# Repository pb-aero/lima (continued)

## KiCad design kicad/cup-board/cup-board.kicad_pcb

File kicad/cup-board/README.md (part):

# Cup board — one schematic for both earcups

**Status (measured 2026-11-09):** preliminary. One A2 sheet, 102 parts, 112 nets. Netlist matches `doc/design_nets.py`;
ERC 0 errors (6 intended strap warnings). All 102 parts have footprints. The PCB is routed: 0 unconnected pads, 2 parity
warnings (U8 value, J12 BOM flag). **Schematic and layout are not reviewed, and no board is recorded as built.** Published to
the shelf as `reports/peter/LIMA_cup_board.html`. Sheet notes corrected 2026-11-09, text only: netlist identical before and
after. The title block is still empty because Konnect has no tool for it; a text note above it identifies the sheet. Set it in
Eeschema's Page Settings.

**⚠ Before any fab or assembly files:** the PCB's U8 value still says `ADP7118AUJZ-3.3-R7`. Set it to the 2.5 V part in pcbnew
(double-click U8 → Value), not with Update PCB from Schematic. The J9–J11 pinouts are placeholders. See "PCB — 72/38 ring".

**How to read this file:** the status, "What's on it" and "Open items" are current. The dated sections below are the record of
how the design got here, and earlier ones are overtaken by later ones; they carry a note where that matters.

Replaces the separate `cup-a-board` / `cup-b-board` first passes (commits `891d746`, `7ffb480`): per Peter, 2026-10-16, both
cups are now **identical**, so there is one board, fitted twice. Cup R is an assembly variant with J11 not fitted (2026-10-30).

This departs from John's Rev G per-cup map (`docs/two-adau1860-channel-allocation.md` §2),
where cup A carried the boom-mic uplink on ADC2 and cup B carried the DVNC accelerometer there.
Here the accelerometer moves off the analog inputs onto TDM, which frees ADC2 on *both* cups,
and the boom mic is replaced by a third MEMS mic. `[gap]` Rev G's upstream slot map has not
been updated to match — see open items.

## What's on it

| Ref | Part | Connection |
|---|---|---|
| U1 | ADAU1861 | Codec, 3 ADC + 1 DAC (ruled 2026-09-22). REG_EN (pin 28) on 1V8, so the internal regulator makes DVDD (pin 54, net `U1_DVDD`, C47 1 µF + C48 100 nF) |
| J9, J10 | 6-pin 0.5 mm ZIF | MK1 feed-forward and MK2 feedback IM73A135 on Infineon flex: 1 `3V3_MIC` (carries 2.5 V), 2–3 output → AINP0/AINN0 and AINP1/AINN1, 4 NC, 5–6/MP GND. **Pinout is a placeholder** |
| J11 | 6-pin 0.5 mm ZIF | MK3 IM72D128 PDM voice mic on flex, cup L only: 1 `1V8`, 2 `DMIC_DATA` → U1 DMIC01, 3 `DMIC_CLK` ← U1, 4–6/MP GND. **Pinout is a placeholder** |
| C11 | 1 µF | 1V8 decoupling, kept on both cups |
| J7 | 6-pin JST GH | In: 1–2 `A_LINE_P/N` (A2B), 3–4 `XF_SEC_A/B` (this cup's SP-74 secondary, from the audio board), 5–6 `ELEC_HI/LO` (boom electret) |
| J8 | 2-pin JST GH | A2B out to the next cup, unused on the last cup |
| J2 | 2-pin JST GH | Earcup driver, 32 Ω: `SPKR_1/2` from the U4/U5 switch commons |
| J12 | 2 solder pads | Boom electret, to J7.5–6 only |
| U4, U5 | Panasonic AQW612S ×2 | Speaker switch K2, one per leg. **Unpowered (N.C., 7–8 closed): speaker ← SP-74 secondary. Driven (N.O., 5–6 closed): speaker ← HPOUTN/HPOUTP** |
| R7, R8, Q2, R17, R18 | 680 Ω ×2, MMBT3904, 2.2 kΩ, 100 kΩ | K2 drive: U6 IO7 → `K2_CTL` → R17 → Q2 (R18 pull-down) switches the LED returns; LEDs fed from `VIN_CUP` |
| C9/C10, R4/R5, R6 | 1 µF ×2, 10 kΩ ×2, 22 kΩ | ADC2 tap off the SP-74 secondary → AINP2/AINN2 |
| U2 | LSM6DSV16BX | DVNC reference, TDM slave into U1's SPT1 (`TDM_DATA/BCLK/WCLK`); I²C for config |
| U3 | MAXM86161 | In-ear optical HR/SpO₂ module. I²C on the local bus, `PPG_INT` → U6 IO0, LED supply from U9 |
| U6 | AD2428 | Bus-powered A2B sub-node. I²S master to U1's SPT0, I²C master on SDA/SCL. See "A2B sub-node" |
| U7, U8, U9 | TPS62161, ADP7118-2.5, ADP7118-3.3 | From `VIN_CUP`: `1V8`; `3V3_MIC` (**net carries 2.5 V**); `VLED` |
| R1/R2, R3 | 10 kΩ | I²C pull-ups to 1V8; U3 INTB pull-up to 1V8 |
| H1, H2 | M2 | Mounting holes |

Everything else is decoupling and the A2B bus networks in "A2B sub-node". **Removed:** MK1–MK3 (now on flex, 2026-10-27),
J3, J4, J6 (2026-10-23), J5 (2026-10-26), T1 (moved to the audio board, 2026-10-20), H3 (2026-10-27).

### MAXM86161 (U3) — how it's wired and why

`[fetched]` from ADI's MAXM86161 datasheet: 14-pin OLGA 2.9 × 4.3 × 1.4 mm; VLED 3.0–5.5 V;
VLDO (internal 1.8 V LDO output) and VREF (1.21 V) are outputs needing only a 1 µF bypass each;
LED drive full-scale up to 124 mA; I²C address fixed at 0x62; INTB open-drain; GPIO open-drain
or sync input; pins 6/7/8 are internally tied to the LED cathodes and must be left unconnected
(solder only).

*Note 2026-11-09: VLED now comes from U9 on this board, J4 is gone, and `PPG_INT` goes to U6 IO0. The reasoning below stands.*

- **VLED has its own rail and connector (J4), deliberately not the 3V3_MIC rail.** 3.3 V would
  just meet the 3.0 V minimum, but the LED driver pulses up to 124 mA, and putting that on the
  bias supply of all three ANC/voice mics would inject LED-rate noise into the audio path.
- **I²C shares SDA/SCL with U1 and U2, no address clash:** U3 0x62 `[fetched]`, U1 0x64
  (`1100 1 ADDR1 ADDR0` with both straps low — `[repo]` `linux/adau1860-pi5/REGISTER_CONFIG.md`,
  Table 22), U2 0x6A with SA0 low `[assumed — ST's standard LSM6 address; not re-read from the
  LSM6DSV16BX datasheet]`. The existing 10 kΩ pull-ups (R1/R2) serve all three.
- **LDO_EN tied to 1V8** — the module is always on whenever both rails are up. Shutdown is still
  available by register.
- **INTB → `PPG_INT`**, pulled up by R3, brought out as a label for whatever host reads the sensor.
- **GPIO no-connect** (power-on default is tristate).

Because all three mic inputs are now differential, U1's `CM` pin is unused and no-connected
(it was only needed to bias the single-ended boom input in the old cup A).

U1 strap pins as on `audio-board`: ADDR0/ADDR1/SELFBOOT/ROM_BOOT_MODE/REG_EN low, PD high.
U2: CS high (I²C), SA0 low, Qvar electrodes to GND, INT1/INT2 no-connect.
SPT0 (`I2S0_*`) connects to U6, the A2B sub-node (2026-10-23).

## 2026-10-26 — brought in line with the redone audio board, per Peter

Three changes, each checked: netlist == `doc/design_nets.py`, ERC 0 errors (6 strap warnings, unchanged) `[measured]`.

1. **U1 DVDD overvoltage fixed.** Pin 54 (DVDD) had been on 1V8 against a **1.21 V absolute maximum**, with pin 28
   REG_EN grounded `[fetched]` ADAU1861 DS (DVDD 0.85–1.21 V; abs max −0.3 to +1.21 V). Now, per the DS pin table:
   **REG_EN → AVDD (1V8)** so the internal regulator makes DVDD; DVDD on its own net `U1_DVDD` with **C47 1 µF + C48
   100 nF** to ground (*"decouple DVDD to DGND with a 1 uF and 0.1 μF capacitor"*); `#FLG10` PWR_FLAG marks the rail
   as internally driven. Commit `f502399`.
2. **Connectors match the audio board, JST GH 1.25 mm** (J7 became 6-pin on 2026-10-29, see "Boom electret pass-through"). J5 is gone. **J7 (4-pin, SM04B):** 1 `A_LINE_P`,
   2 `A_LINE_N`, 3 `XF_SEC_A`, 4 `XF_SEC_B` — the same order as the audio board's J3 (A2B+, A2B−, speaker pair), so a
   straight 1:1 GH cable joins audio J3 → cup L J7. **J8 (2-pin, SM02B):** A2B out to the next cup. **J2 (2-pin, SM02B):**
   speaker driver. **Cup R needs a split harness into its J7:** pins 1–2 from cup L's J8, pins 3–4 from the audio
   board's J4 — the cost of one board for both cups. (Alternative if that harness is unwelcome: a 6-pin chain that
   carries cup R's speaker pair through cup L — changes the audio board's J3/J4 too. Not done.)
3. **`PPG_INT` → U6 IRQ/IO0 (pin 6).** `[fetched]` AD242x DS Table 15: in slave mode, when not used for mailbox
   interrupts, IRQ/IO0 *"serves as a general-purpose I/O pin with interrupt request input capability"*. MAXM86161 INTB
   is open-drain, pulled up to 1V8 by R3; U6 IOVDD is 1V8, so levels match. Software: configure IO0 as an input with
   falling-edge interrupt; the CM5 already polls `A2B_INTSTAT` (audio-board ruling 11). Not yet checked against the TRM
   register list.

## A2B sub-node — 2026-10-23, per Peter

Peter: *"lets try io7 and add a2b to the cup board"*. The cup is now a **bus-powered AD2428 sub-node** (U6): no power wires
in the cup cable, so everything on the board runs from the A2B bias. Intended connectivity is `doc/design_nets.py` —
the netlist at `b641179` plus these edits — and `python3 -I doc/design_nets.py check <netlist.xml>` diffs it against
the kicad-cli netlist. **Result: OK** (every pre-existing net unchanged, every new net complete) `[measured]`.
ERC 0 errors; 6 warnings, all strap pins tied to rails (the 4 old ones plus U6 ADR1/ADR2). The two single-pin
`I2S0_*` warnings are gone — U6 terminates them.

| Block | Parts | Source |
|---|---|---|
| A side (upstream, J7) | FB1/FB2→ACM (+C12 330 nF), C13 12 pF, L1/L2 180 nH, C14/C15 27 pF, FL1 CMC, R9/R10 120R + C16/C17 33 nF, C18/C19 10 nF series, C20/C21 33 nF, C22 470 nF across | EVAL-AD2428WD1BZ sheet 2, A side, read from a rendered image `[fetched]` |
| Bus power in | L3 (line+ → V_NODE), L4 (line− → GND), D1 ZLLS400 → VIN_CUP, C23/C24 | AD242x DS Fig. 36 (bus-powered sub-node) `[fetched]` |
| B side (downstream, J8) | Q1 AO3401A switched by SWP (R11–R14, C25/C26), L5/L6, same coupling as the audio board's main node | DS Fig. 36 + eval B side |
| U6 | I²S master: DTX0 → `I2S0_SDATAI`, DRX0 ← `I2S0_SDATAO`, BCLK/SYNC → `I2S0_BCLK`/`I2S0_FSYNC`; I²C master on SDA/SCL; IOVDD on 1V8; VOUT1/VOUT2 decoupled | AD242x TRM |
| K2 drive | U6 IO7 → R17 2.2k → Q2 MMBT3904 (R18 100k pull-down) switches U4/U5 LED returns; R7/R8 **680R** from VIN_CUP (220R until the 8 V bus) | audio-board rulings 11, 12 |
| Power | U7 TPS62161 → 1V8, U8 ADP7118-**2.5** → 3V3_MIC (**2.5 V since 2026-10-30**; the 3.3 V part exceeded the IM73A135's 3.0 V abs max; net name kept to spare the routing), U9 ADP7118-3.3 → VLED (separate, as before, to keep PPG pulses off the mic rail) | TPS6216x DS, ADP7118 |

**Removed:** J3 (1V8/3V3_MIC in), J4 (VLED in), J6 (`SW_DRV` in), and the PWR_FLAGs on 3V3_MIC/VLED (the LDOs drive
them now). **Why a BJT for K2:** U6's IO is 1.8 V, too low to turn a 2N7002 on reliably. **Why 680R:** with the AeroNode's 8 V bus (ruling 12) VIN_CUP is 6.4–7.2 V, giving 5.1–7.2 mA per string
(220R would have pushed ~20 mA and wasted ~0.27 W per cup).

**Ground rule `[fetched]` EE-419:** *"the ground of a bus-powered node is not at the same potential as the ground of a
locally-powered node ... only floating signals ... should be connected."* J5 (SP-74 secondary) is transformer-isolated
and reaches U1 only through C9/C10; the speaker reaches it only through K2. The IO7 route also avoided a wired K2 drive
that would have DC-tied the grounds.

### Open — A2B sub-node

- ~~**VIN_CUP margin at low battery.**~~ **Closed 2026-10-23:** `docs/a2b-bus-power-budget.md` → 8 V boost on the audio
  board (ruling 12); cup R VIN 6.44 V worst case.
- ~~**Cup power budget not run**~~ **Run 2026-10-30** — see "Power budget — 2026-10-30": ≈ 41–45 mA per cup normal,
  149 mA for both cups worst case, inside the 300 mA VSSN limit. (Original item:) (U1's HiFi 3z, three mics, LSM6, MAXM86161 LED pulses) against the main node's 300 mA
  VSSN limit for both cups.
- **Sub-node IO7 state on data-link loss with bus power still up** — not in the TRM section read.
- **Cup R's speaker pair** arrives on its J7.3–4 from the audio board's J4; A2B comes from cup L's J8 on J7.1–2.
- ~~**Still unfixed, needs Peter's go-ahead:** U1 DVDD (pin 54) on 1V8 against a 1.21 V abs max (REG_EN low).~~
  **Fixed 2026-10-26** (internal regulator, see above).

## Aircraft audio in — 2026-10-20, per Peter

*Note 2026-11-09: this section's J5 is now J7.3–4, its `SW_DRV`/J6 is now the K2 drive from U6 IO7, and its "T1" is this cup's
SP-74 on the audio board. Its 330 Ω and 5 V drive figures are replaced by 680 Ω from `VIN_CUP`, 5.1–7.2 mA per string.*

Peter ruled: aircraft audio goes into **ADC2 on each cup** (MK3 dropped), the speaker is
**32 Ω**, and the cup must **still be heard unpowered** (fail-passive). Peter proposed the
SP-74 for the bypass path.

```
   audio board                    cable    cup board
 Ring ──┐                 ┌─ J6/J7 ─────── J5 XF_SEC_A ──┬── U4/U5 N.C. ─┐
        SP-74 (pri)   SP-74 (2 sec ∥)                   │               ├─ SPKR_1/2 ── J2 speaker 32 Ω
 Sleeve ┘  T2 / T3        └─ J6/J7 ─────── J5 XF_SEC_B ──┼── U4/U5 N.C. ─┘   U4/U5 N.O. ── HPOUTN / HPOUTP
                                             └── C9/R4, C10/R5, R6 ── AINP2 / AINN2
```

- **Unpowered, or `SW_DRV` dropped:** U4/U5's N.C. switches are closed and T1 drives the speaker. `[derived]` With
  the full primary and the two secondaries in parallel, the turns ratio is 3.143:1, so the
  impedance ratio is 9.88:1 and a 32 Ω speaker looks like **≈ 316 Ω** to the panel. Two cups
  on a mono panel come to ≈ 158 Ω, which is inside the ≥ 150 Ω the panel is rated for.
  `[fetched]` The Garmin GMA 340 is specified at 100 mW per channel into 150 Ω. Against the
  120 Ω series resistor considered first, the transformer is ≈ 3.6 dB louder at the same panel
  voltage and halves the panel loading. Triad's own rating is 80 Ω : **32 Ω with the secondaries
  in series**, or 8 Ω in parallel. We deliberately use the parallel connection with a 32 Ω load,
  so the panel sees 316 Ω and not 80 Ω.
  **Correction, 2026-10-21:** the SP-74 has **no primary centre tap.** DigiKey's "80 CT"
  description is wrong, and Triad's drawing shows pins 1–2 only. My 2026-10-20 note that "the
  centre tap would give 79 Ω" was built on that listing and is withdrawn. The conclusion stands,
  because the full primary was the connection used anyway.

### SP-74 pinout — `[fetched]` Triad datasheet, publish date 2024-05-30 (`docs/datasheets/Triad_SP-74.pdf`)

| Pin | Winding | Dot | Net here |
|---|---|---|---|
| 1 | Primary, 80 Ω, 12.5 Ω DCR | ● | `RX_RING` (audio board; was `AC_AUDIO` here) |
| 2 | Primary | | `AC_GND` (audio board) |
| 3 | Secondary 1 | ● | `XF_SEC_A` |
| 4 | Secondary 1 | | `XF_SEC_B` |
| 5 | Secondary 2 | ● | `XF_SEC_A` |
| 6 | Secondary 2 | | `XF_SEC_B` |

- **Parallel (8 Ω, this design):** 3∥5 and 4∥6, dot to dot. **Series (32 Ω):** link 4–5 and
  take the output across 3–6.
- **Package:** six gold-plated 0.020″ pins, with a tab at pin 1. The body is
  0.410 × 0.310 × 0.465″ max and the leads are 0.750″ min.
  `[derived]` **Two rows of three: 1-3-5 and 2-4-6, with 2 opposite 1, 4 opposite 3 and 6
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
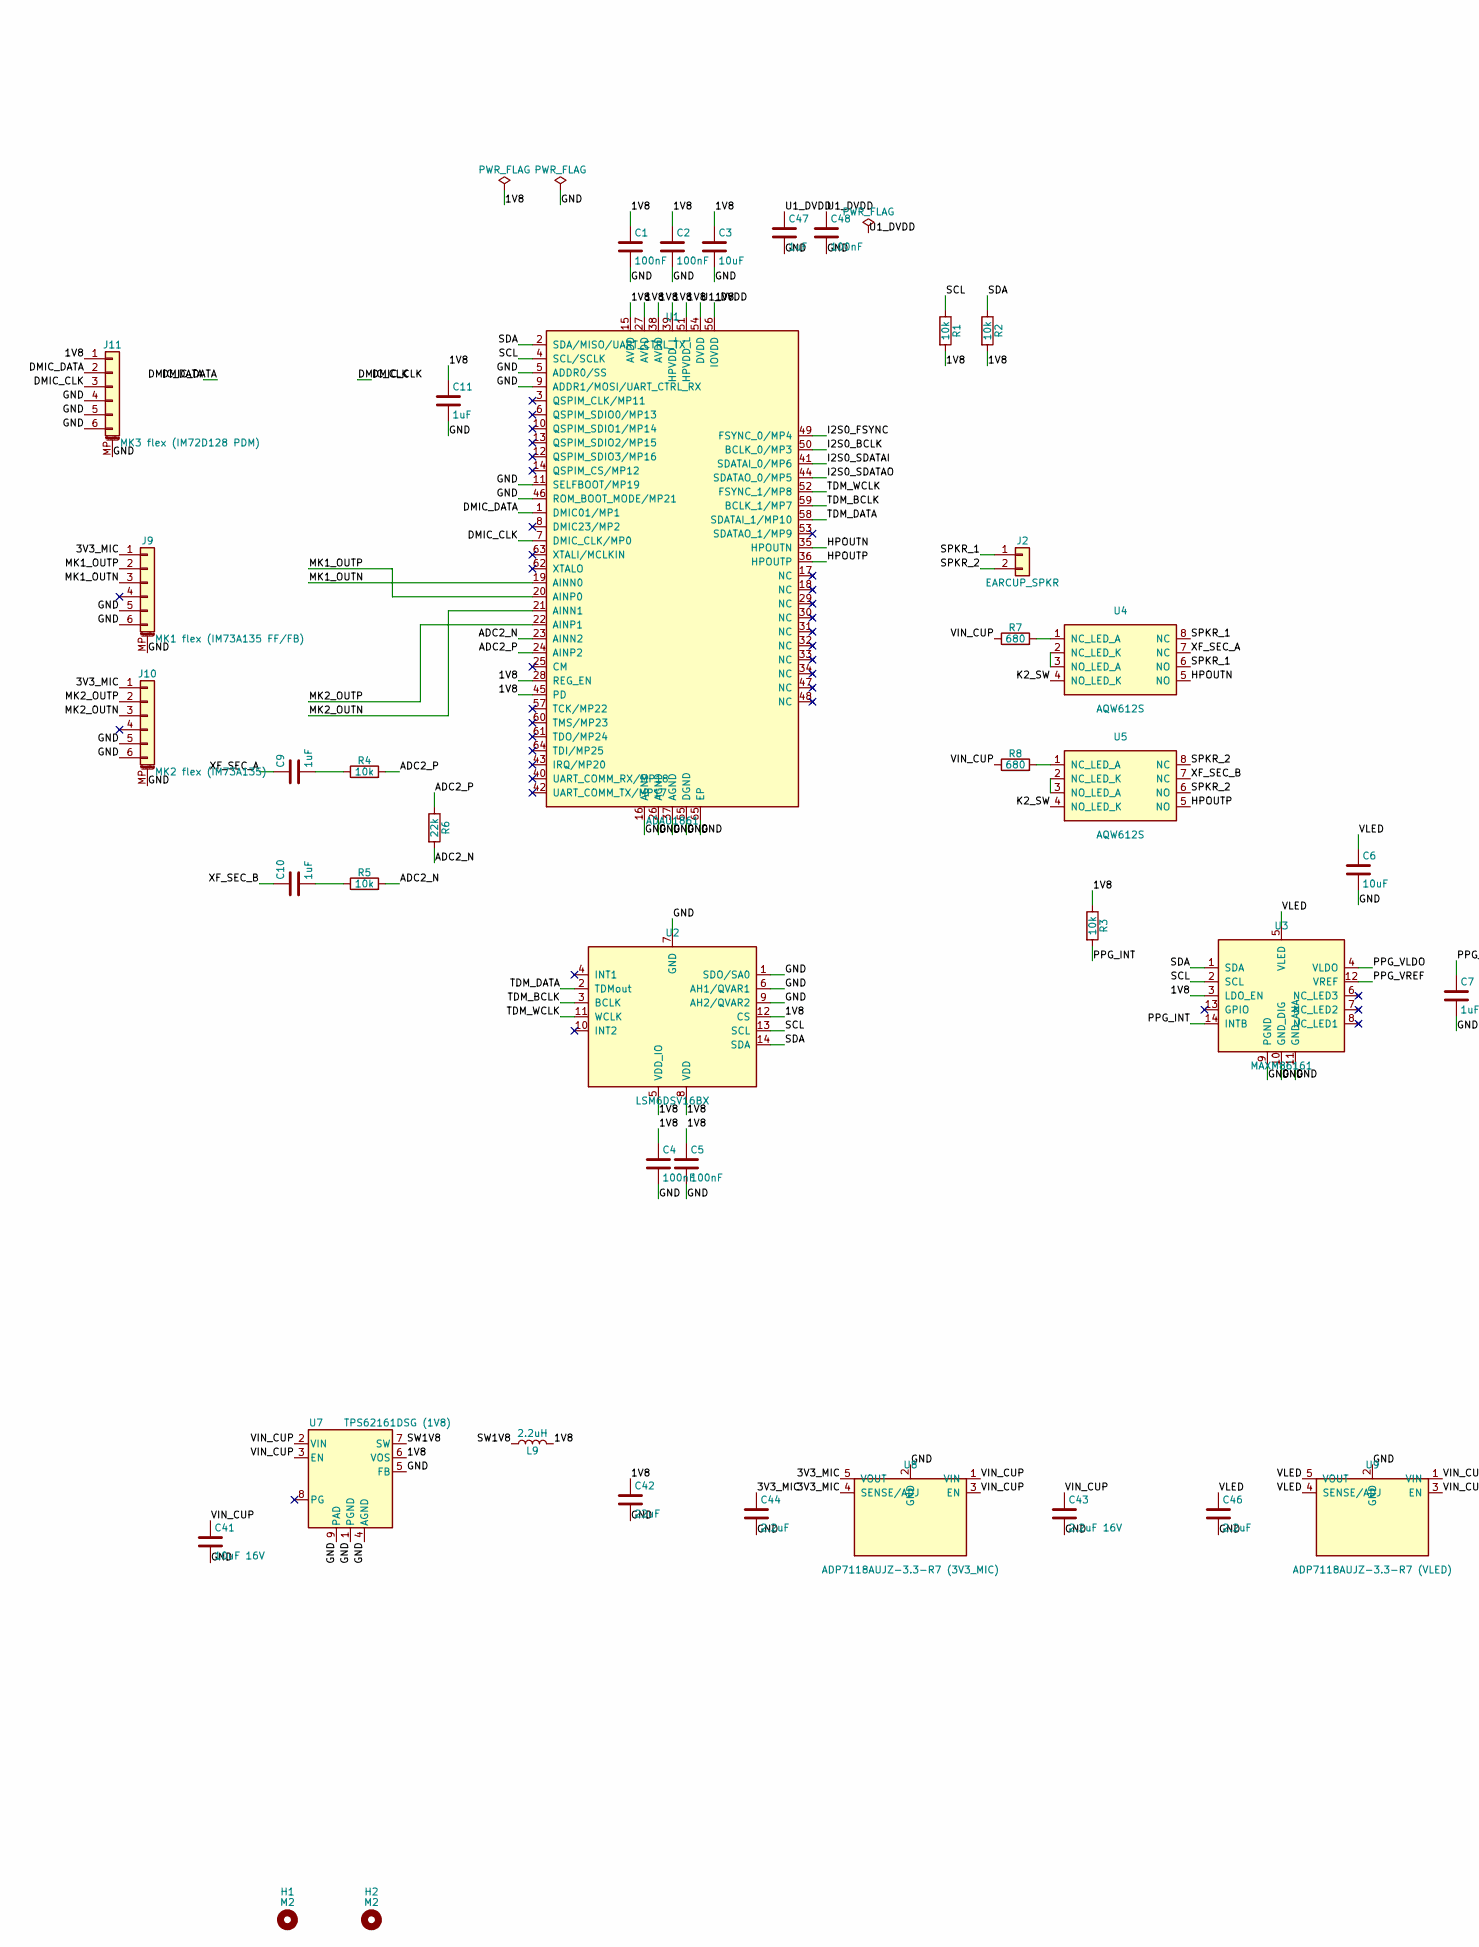
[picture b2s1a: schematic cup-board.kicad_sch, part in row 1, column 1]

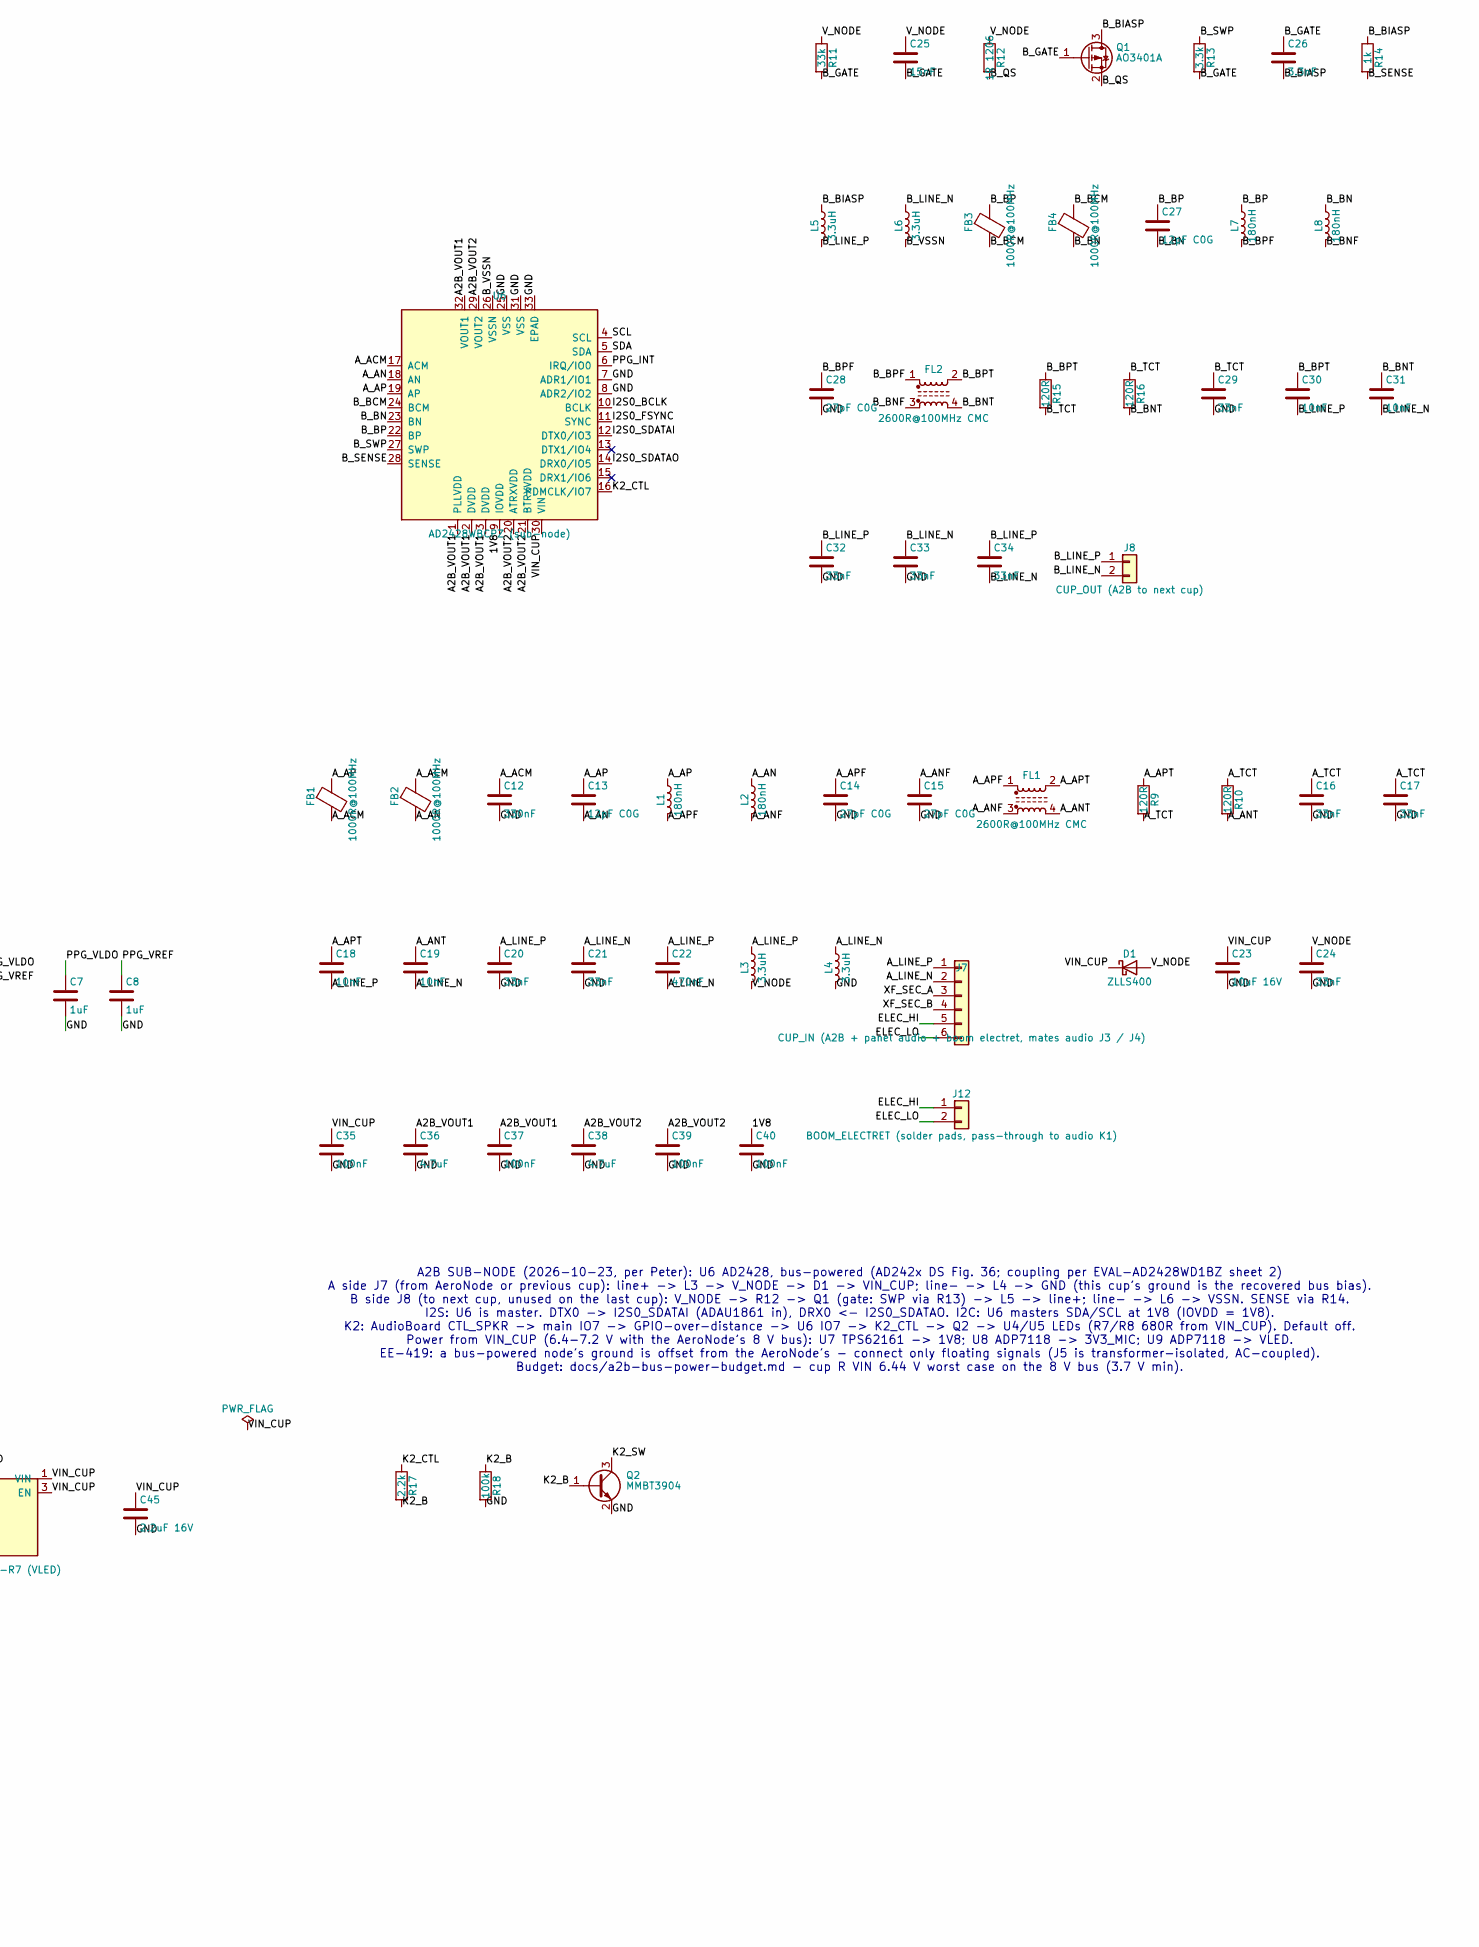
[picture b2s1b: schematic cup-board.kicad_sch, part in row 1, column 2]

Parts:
C1, C2, C4, C5, C35, C37, C39, C40, C48: 100nF; C_0603_1608Metric
C3, C6: 10uF; C_0805_2012Metric
C7, C8, C9, C10, C11, C47: 1uF; C_0603_1608Metric
C12: 330nF; C_0603_1608Metric
C13, C27: 12pF C0G; C_0603_1608Metric
C14, C15, C28: 27pF C0G; C_0603_1608Metric
C16, C17, C20, C21, C24, C29, C32, C33, C34: 33nF; C_0603_1608Metric
C18, C19, C30, C31: 10nF; C_0603_1608Metric
C22: 470nF; C_0603_1608Metric
C23, C41: 10uF 16V; C_0805_2012Metric
C25: 15nF; C_0603_1608Metric
C26: 3.3nF; C_0603_1608Metric
C36, C38: 4.7uF; C_0603_1608Metric
C42: 22uF; C_0805_2012Metric
C43, C45: 2.2uF 16V; C_0603_1608Metric
C44, C46: 2.2uF; C_0603_1608Metric
D1: ZLLS400; D_SOD-323
FB1, FB2, FB3, FB4: 1000R@100MHz; L_0603_1608Metric
FL1, FL2: 2600R@100MHz CMC; L_CommonModeChoke_Coilank_ACM3216
H1, H2: M2; MountingHole_2.2mm_M2
J2: EARCUP_SPKR; JST_GH_SM02B-GHS-TB_1x02-1MP_P1.25mm_Horizontal
J7: CUP_IN (A2B + panel audio + boom electret, mates 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; JST_GH_SM06B-GHS-TB_1x06-1MP_P1.25mm_Horizontal
J8: CUP_OUT (A2B to next cup); JST_GH_SM02B-GHS-TB_1x02-1MP_P1.25mm_Horizontal
J9: MK1 flex (IM73A135 FF/FB); Hirose_FH12-6S-0.5SH_1x06-1MP_P0.50mm_Horizontal; MPN Hirose FH12-6S-0.5SH(55)
J10: MK2 flex (IM73A135); Hirose_FH12-6S-0.5SH_1x06-1MP_P0.50mm_Horizontal; MPN Hirose FH12-6S-0.5SH(55)
J11: MK3 flex (IM72D128 PDM); Hirose_FH12-6S-0.5SH_1x06-1MP_P0.50mm_Horizontal; MPN Hirose FH12-6S-0.5SH(55)
J12: BOOM_ELECTRET (solder pads, pass-through to audio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; SolderWire-0.15sqmm_1x02_P4mm_D0.5mm_OD1.5mm
L1, L2, L7, L8: 180nH; L_0603_1608Metric
L3, L4, L5, L6: 3.3uH; L_1210_3225Metric
L9: 2.2uH; L_1008_2520Metric
Q1: AO3401A; SOT-23
Q2: MMBT3904; SOT-23
R1, R2, R3, R4, R5: 10k; R_0603_1608Metric
R6: 22k; R_0603_1608Metric
R7, R8: 680; R_0603_1608Metric
R9, R10, R15, R16: 120R; R_0603_1608Metric
R11: 33k; R_0603_1608Metric
R12: 1R 1206; R_1206_3216Metric
R13: 3.3k; R_0603_1608Metric
R14: 1k; R_0603_1608Metric
R17: 2.2k; R_0603_1608Metric
R18: 100k; R_0603_1608Metric
U1: ADAU1861; AD_LFCSP-SS-64-1EP_9x9mm_P0.5mm_EP6.3x6.3mm_CS-64-2
U2: LSM6DSV16BX; LGA-14_3x2.5mm_P0.5mm_LayoutBorder3x4y
U3: MAXM86161; Maxim_OLGA-14_2.9x4.3mm_P0.6mm_F142A4_MAXM86161
U4, U5: AQW612S; Panasonic_GU-SOP8_4.4x9.37mm_P2.54mm_AQW61xS
U6: AD2428WBCPZ (sub-node); QFN-32-1EP_5x5mm_P0.5mm_EP3.6x3.6mm_ThermalVias
U7: TPS62161DSG (1V8); WSON-8-1EP_2x2mm_P0.5mm_EP0.9x1.6mm_ThermalVias
U8: ADP7118AUJZ-3.3-R7 (3V3_MIC); TSOT-23-5
U9: ADP7118AUJZ-3.3-R7 (VLED); TSOT-23-5

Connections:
/1V8: C1.1, C2.1, C3.1, C4.1, C5.1, C11.1, C40.1, C42.1, J11.1, L9.2, R1.2, R2.2, R3.1, U1.15 (AVDD), U1.27 (AVDD), U1.28 (REG_EN), U1.38 (AVDD), U1.39 (HPVDD_L), U1.45 (PD), U1.51 (HPVDD_L), U1.56 (IOVDD), U2.5 (VDD_IO), U2.8 (VDD), U2.12 (CS), U3.3 (LDO_EN), U6.9 (IOVDD), U7.6 (VOS)
/3V3_MIC: C44.1, J9.1, J10.1, U8.4 (SENSE/ADJ), U8.5 (VOUT)
/A2B_VOUT1: C36.1, C37.1, U6.1 (PLLVDD), U6.2 (DVDD), U6.3 (DVDD), U6.32 (VOUT1)
/A2B_VOUT2: C38.1, C39.1, U6.20 (ATRXVDD), U6.21 (BTRXVDD), U6.29 (VOUT2)
/ADC2_N: R5.2, R6.2, U1.23 (AINN2)
/ADC2_P: R4.2, R6.1, U1.24 (AINP2)
/A_ACM: C12.1, FB1.2, FB2.1, U6.17 (ACM)
/A_AN: C13.2, FB2.2, L2.1, U6.18 (AN)
/A_ANF: C15.1, FL1.3, L2.2
/A_ANT: C19.1, FL1.4, R10.2
/A_AP: C13.1, FB1.1, L1.1, U6.19 (AP)
/A_APF: C14.1, FL1.1, L1.2
/A_APT: C18.1, FL1.2, R9.1
/A_LINE_N: C19.2, C21.1, C22.2, J7.2, L4.1
/A_LINE_P: C18.2, C20.1, C22.1, J7.1, L3.1
/A_TCT: C16.1, C17.1, R9.2, R10.1
/B_BCM: FB3.2, FB4.1, U6.24 (BCM)
/B_BIASP: C26.2, L5.1, Q1.3 (D), R14.1
/B_BN: C27.2, FB4.2, L8.1, U6.23 (BN)
/B_BNF: FL2.3, L8.2
/B_BNT: C31.1, FL2.4, R16.2
/B_BP: C27.1, FB3.1, L7.1, U6.22 (BP)
/B_BPF: C28.1, FL2.1, L7.2
/B_BPT: C30.1, FL2.2, R15.1
/B_GATE: C25.2, C26.1, Q1.1 (G), R11.2, R13.2
/B_LINE_N: C31.2, C33.1, C34.2, J8.2, L6.1
/B_LINE_P: C30.2, C32.1, C34.1, J8.1, L5.2
/B_QS: Q1.2 (S), R12.2
/B_SENSE: R14.2, U6.28 (SENSE)
/B_SWP: R13.1, U6.27 (SWP)
/B_TCT: C29.1, R15.2, R16.1
/B_VSSN: L6.2, U6.26 (VSSN)
/DMIC_CLK: J11.3, U1.7 (DMIC_CLK/MP0)
/DMIC_DATA: J11.2, U1.1 (DMIC01/MP1)
/ELEC_HI: J7.5, J12.1
/ELEC_LO: J7.6, J12.2
/GND: C1.2, C2.2, C3.2, C4.2, C5.2, C6.2, C7.2, C8.2, C11.2, C12.2, C14.2, C15.2, C16.2, C17.2, C20.2, C21.2, C23.2, C24.2, C28.2, C29.2, C32.2, C33.2, C35.2, C36.2, C37.2, C38.2, C39.2, C40.2, C41.2, C42.2, C43.2, C44.2, C45.2, C46.2, C47.2, C48.2, J9.5, J9.6, J9.MP (MountPin), J10.5, J10.6, J10.MP (MountPin), J11.4, J11.5, J11.6, J11.MP (MountPin), L4.2, Q2.2 (E), R18.2, U1.5 (ADDR0/SS), U1.9 (ADDR1/MOSI/UART_CTRL_RX), U1.11 (SELFBOOT/MP19), U1.16 (AGND), U1.26 (AGND), U1.37 (AGND), U1.46 (ROM_BOOT_MODE/MP21), U1.55 (DGND), U1.65 (EP), U2.1 (SDO/SA0), U2.6 (AH1/QVAR1), U2.7 (GND), U2.9 (AH2/QVAR2), U3.9 (PGND), U3.10 (GND_DIG), U3.11 (GND_ANA), U6.7 (ADR1/IO1), U6.8 (ADR2/IO2), U6.25 (VSS), U6.31 (VSS), U6.33 (EPAD), U7.1 (PGND), U7.4 (AGND), U7.5 (FB), U7.9 (PAD), U8.2 (GND), U9.2 (GND)
/HPOUTN: U1.35 (HPOUTN), U4.5 (NO)
/HPOUTP: U1.36 (HPOUTP), U5.5 (NO)
/I2S0_BCLK: U1.50 (BCLK_0/MP3), U6.10 (BCLK)
/I2S0_FSYNC: U1.49 (FSYNC_0/MP4), U6.11 (SYNC)
/I2S0_SDATAI: U1.41 (SDATAI_0/MP6), U6.12 (DTX0/IO3)
/I2S0_SDATAO: U1.44 (SDATAO_0/MP5), U6.14 (DRX0/IO5)
/K2_B: Q2.1 (B), R17.2, R18.1
/K2_CTL: R17.1, U6.16 (PDMCLK/IO7)
/K2_SW: Q2.3 (C), U4.4 (NO_LED_K), U5.4 (NO_LED_K)
/MK1_OUTN: J9.3, U1.19 (AINN0)
/MK1_OUTP: J9.2, U1.20 (AINP0)
/MK2_OUTN: J10.3, U1.21 (AINN1)
/MK2_OUTP: J10.2, U1.22 (AINP1)
/PPG_INT: R3.2, U3.14 (INTB), U6.6 (IRQ/IO0)
/PPG_VLDO: C7.1, U3.4 (VLDO)
/PPG_VREF: C8.1, U3.12 (VREF)
/SCL: R1.1, U1.4 (SCL/SCLK), U2.13 (SCL), U3.2 (SCL), U6.4 (SCL)
/SDA: R2.1, U1.2 (SDA/MISO/UART_CTRL_TX), U2.14 (SDA), U3.1 (SDA), U6.5 (SDA)
/SPKR_1: J2.1, U4.6 (NO), U4.8 (NC)
/SPKR_2: J2.2, U5.6 (NO), U5.8 (NC)
/SW1V8: L9.1, U7.7 (SW)
/TDM_BCLK: U1.59 (BCLK_1/MP7), U2.3 (BCLK)
/TDM_DATA: U1.58 (SDATAI_1/MP10), U2.2 (TDMout)
/TDM_WCLK: U1.52 (FSYNC_1/MP8), U2.11 (WCLK)
/U1_DVDD: C47.1, C48.1, U1.54 (DVDD)
/VIN_CUP: C23.1, C35.1, C41.1, C43.1, C45.1, D1.1 (K), R7.1, R8.1, U6.30 (VIN), U7.2 (VIN), U7.3 (EN), U8.1 (VIN), U8.3 (EN), U9.1 (VIN), U9.3 (EN)
/VLED: C6.1, C46.1, U3.5 (VLED), U9.4 (SENSE/ADJ), U9.5 (VOUT)
/V_NODE: C24.1, C25.1, D1.2 (A), L3.2, R11.1, R12.1
/XF_SEC_A: C9.1, J7.3, U4.7 (NC)
/XF_SEC_B: C10.1, J7.4, U5.7 (NC)
unnamed: C9.2, R4.1
unnamed: C10.2, R5.1
unnamed: R7.2, U4.1 (NC_LED_A)
unnamed: U4.2 (NC_LED_K), U4.3 (NO_LED_A)
unnamed: R8.2, U5.1 (NC_LED_A)
unnamed: U5.2 (NC_LED_K), U5.3 (NO_LED_A)

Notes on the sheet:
A2B SUB-NODE (2026-10-23, per Peter): U6 AD2428, bus-powered (AD242x DS Fig. 36; coupling per EVAL-AD2428WD1BZ sheet 2) A side J7 (from AeroNode or previous cup): line+ -> L3 -> V_NODE -> D1 -> VIN_CUP; line- -> L4 -> GND (this cup's ground is the recovered bus bias). B side J8 (to next cup, unused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

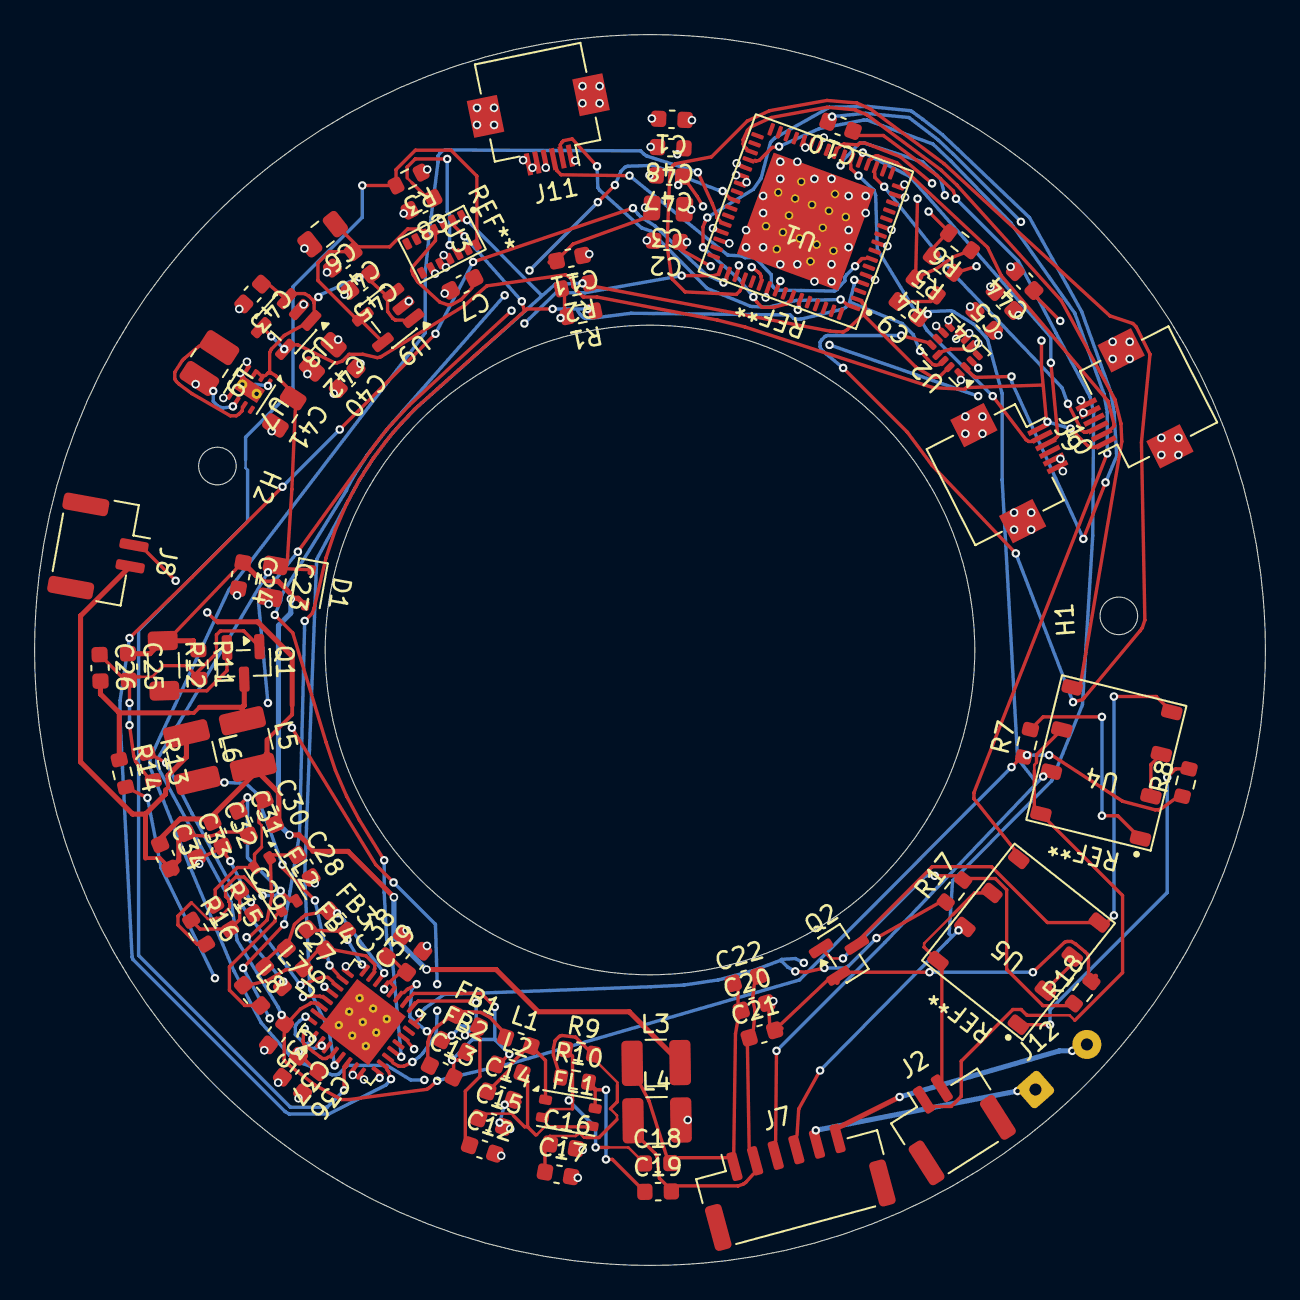
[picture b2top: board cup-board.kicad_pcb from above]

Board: 4 copper layers, 72.0 x 72.0 mm, 102 parts (0 on the bottom side), 73 nets.

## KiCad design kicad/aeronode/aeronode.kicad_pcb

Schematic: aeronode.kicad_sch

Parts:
C1, C9, C10, C11, C12, C15, C18: 10uF; C_0603_1608Metric
C2: 47uF; C_0805_2012Metric
C3, C13, C14, C16, C17, C19, C20, C21, C22: 100nF; C_0402_1005Metric
C4: 1uF; C_0603_1608Metric
C5: 0.22uF; C_0402_1005Metric
C6, C7: 47nF; C_0402_1005Metric
C8: 4.7uF; C_0603_1608Metric
D1: CHG; LED_0603_1608Metric
D2: RED; LED_0603_1608Metric
D3: GREEN; LED_0603_1608Metric
D4: BLUE; LED_0603_1608Metric
J1: IMU_BOARD; PinHeader_2x10_P2.54mm_Vertical
J2: USB-C PD / recovery; USB_C_Receptacle_HCTL_HC-TYPE-C-16P-01A
J3: 2S LiFePO4 6Ah + BMS; PinHeader_1x03_P2.54mm_Vertical
L1: 4.7uH; L_Bourns-SRN6028
L2: 1.0uH; L_Bourns-SRN4018
Q1: NMOS pass - TBD; SOT-23
R1, R9, R14: 100k; R_0402_1005Metric
R2: 6.04k; R_0402_1005Metric
R3, R5, R7, R8: 5.1k; R_0402_1005Metric
R4, R6, R15: 1k; R_0402_1005Metric
R10: 24.9k; R_0402_1005Metric
R11, R12, R13, R17, R19, R21, R31: 10k; R_0402_1005Metric
R16: 34k; R_0402_1005Metric
R18: 22.1k; R_0402_1005Metric
R20: 30.1k; R_0402_1005Metric
R22: 15m; R_1206_3216Metric
R23: 5.24k; R_0402_1005Metric
R24: 30.31k; R_0402_1005Metric
R25, R26: 4.7k; R_0402_1005Metric
R27: 100R; R_0402_1005Metric
R28: 160R; R_0402_1005Metric
R29: 150R; R_0402_1005Metric
R30: 68R; R_0402_1005Metric
SW1: ON/OFF; SW_Push_1P1T_NO_CK_KMR2
U1: ConnectCore93_LGA; Digi_ConnectCore93_LGA
U2: CYPD3177-24LQ; QFN-24-1EP_4x4mm_P0.5mm_EP2.75x2.75mm
U3: BQ25798; Texas_RQM0029A_VQFN-29_4x4mm_P0.4mm
U4: LMR33630ADDA; Texas_HSOP-8-1EP_3.9x4.9mm_P1.27mm_ThermalVias
U5: LTC4364CMS; MSOP-16_3x4.039mm_P0.5mm
U6: BME690; Bosch_LGA-8_3x3mm_P0.8mm_ClockwisePinNumbering; MPN BME690
U7: DAN-F10N; ublox_DAN-F10N; MPN DAN-F10N-00B
U9: MMC5983MA; LGA-16_3x3mm_P0.5mm; MPN MMC5983MA
U10: BMP390; Bosch_BMP390_LGA-10_2x2mm; MPN BMP390

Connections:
/+1V8: U1.AH1 (1V8), U1.AH2 (1V8), U1.AH3 (1V8), U1.E5 (1V8)
/+3V3: C13.1, C14.1, C15.1, C16.1, C19.1, C20.1, C21.1, C22.1, J1.1, R11.1, R12.1, R13.1, R14.1, R15.1, R25.1, R26.1, R28.1, R29.1, R30.1, R31.1, U1.AK1 (3V3), U1.AL2 (3V3), U1.AL3 (3V3), U1.AM3 (3V3), U1.AM4 (3V3), U6.2 (CSB), U6.6 (VDDIO), U6.8 (VDD), U7.52 (VCC), U7.53 (VCC), U7.55 (V_BCKP), U9.2 (VDD), U9.4 (SPI_CS), U9.13 (VDDIO), U10.1 (VDDIO), U10.6 (CSB), U10.10 (VDD)
/+5V: R20.1, R22.2, U1.AJ2 (VSYS2), U1.AJ3 (VSYS2), U1.AJ4 (VSYS2), U1.AK2 (VSYS2), U1.AK3 (VSYS2), U1.AK4 (VSYS2), U1.AL6 (VSYS), U1.AL7 (VSYS), U1.AL8 (VSYS), U5.1 (OUT)
/+5V_RAW: C2.1, L1.2, Q1.3 (D), R9.1, R16.1, R18.1, U5.8 (VCC), U5.9 (~SHDN)
/BARO_SA0: R31.2, U10.5 (SDO)
/BAT_TS: J3.2, R23.2, R24.1, U3.16 (TS)
/BMI_ACC_CS: J1.16, U1.P1 (UART7_TX)
/BMI_ACC_INT: J1.19, U1.AA1 (GPIO2_IO06)
/BMI_GYR_CS: J1.17, U1.C24 (GPIO2_IO24)
/BMI_GYR_INT: J1.20, U1.Y1 (GPIO1_IO10)
/BMI_MOSI: J1.13, U1.M29 (UART7_CTS)
/BMI_SCLK: J1.11, U1.N29 (UART7_RTS)
/BMI_SDO: J1.14, J1.15, U1.R1 (UART7_RX)
/BOOT_5V: C3.1, U4.7 (BOOT)
/CC1: J2.A5 (CC1), U2.15 (CC1)
/CC2: J2.B5 (CC2), U2.14 (CC2)
/CHG_BTST1: C6.1, U3.4 (BTST1)
/CHG_BTST2: C7.1, U3.19 (BTST2)
/CHG_CE_N: R1.2, U1.AN4 (GPIO2_IO18), U3.13 (~CE)
/CHG_INT_N: R13.2, U1.E3 (GPIO2_IO19), U3.21 (~INT)
/CHG_LED_A: D1.2 (A), R15.2
/CHG_PMID: C10.1, U3.29 (PMID)
/CHG_PROG: R2.1, U3.20 (PROG)
/CHG_SCL: R11.2, U1.V1 (I2C2_SCL), U3.14 (SCL)
/CHG_SDA: R12.2, U1.W1 (I2C2_SDA), U3.15 (SDA)
/CHG_STAT_N: D1.1 (K), U3.1 (STAT)
/CHG_SW1: C6.2, L2.1, U3.28 (SW1)
/CHG_SW2: C7.2, L2.2, U3.26 (SW2)
/FB_5V: R9.2, R10.1, U4.5 (FB)
/GND: C1.2, C2.2, C4.2, C5.2, C8.2, C9.2, C10.2, C11.2, C12.2, C13.2, C14.2, C15.2, C16.2, C17.2, C18.2, C19.2, C20.2, C21.2, C22.2, J1.2, J1.4, J1.8, J1.12, J1.18, J2.A1 (GND), J2.A12 (GND), J2.B1 (GND), J2.B12 (GND), J2.SH (SHIELD), J3.3, R2.2, R4.2, R6.2, R8.2, R10.2, R17.2, R19.2, R21.2, R24.2, SW1.2, U1.A4 (GND), U1.A5 (GND), U1.A25 (GND), U1.AF2 (GND), U1.AF3 (GND), U1.AF4 (GND), U1.AF5 (GND), U1.AF6 (GND), U1.AF7 (GND), U1.AF8 (GND), U1.AF9 (GND), U1.AF10 (GND), U1.AF11 (GND), U1.AF12 (GND), U1.AF13 (GND), U1.AF14 (GND), U1.AF15 (GND), U1.AF16 (GND), U1.AF17 (GND), U1.AF18 (GND), U1.AF19 (GND), U1.AF20 (GND), U1.AF21 (GND), U1.AF22 (GND), U1.AF23 (GND), U1.AF24 (GND), U1.AF25 (GND), U1.AF26 (GND), U1.AF27 (GND), U1.AF28 (GND), U1.AG2 (GND), U1.AG3 (GND), U1.AG4 (GND), U1.AG5 (GND), U1.AG6 (GND), U1.AG7 (GND), U1.AG16 (GND), U1.AG23 (GND), U1.AH4 (GND), U1.AH5 (GND), U1.AH8 (GND), U1.AH14 (GND), U1.AH17 (GND), U1.AH19 (GND), U1.AH21 (GND), U1.AJ1 (GND), U1.AJ5 (GND), U1.AJ6 (GND), U1.AJ7 (GND), U1.AJ9 (GND), U1.AJ14 (GND), U1.AJ17 (GND), U1.AJ20 (GND), U1.AJ26 (GND), U1.AK5 (GND), U1.AK6 (GND), U1.AK7 (GND), U1.AK8 (GND), U1.AK9 (GND), U1.AK10 (GND), U1.AK11 (GND), U1.AK12 (GND), U1.AK13 (GND), U1.AK14 (GND), U1.AK17 (GND), U1.AK20 (GND), U1.AK23 (GND), U1.AL4 (GND), U1.AL5 (GND), U1.AL9 (GND), U1.AL10 (GND), U1.AL11 (GND), U1.AL14 (GND), U1.AL17 (GND), U1.AM5 (GND), U1.AM6 (GND), U1.AM12 (GND), U1.AM15 (GND), U1.AM18 (GND), U1.AM20 (GND), U1.AN8 (GND), U1.AN11 (GND), U1.AN14 (GND), U1.AN17 (GND), U1.AN20 (GND), U1.B3 (GND), U1.B4 (GND), U1.B5 (GND), U1.B8 (GND), U1.B11 (GND), U1.B14 (GND), U1.B15 (GND), U1.B18 (GND), U1.B25 (GND), U1.B26 (GND), U1.B27 (GND), U1.C2 (GND), U1.C4 (GND), U1.C5 (GND), U1.C12 (GND), U1.C13 (GND), U1.C14 (GND), U1.C15 (GND), U1.C16 (GND), U1.C25 (GND), U1.C26 (GND), U1.C28 (GND), U1.D2 (GND), U1.D3 (GND), U1.D4 (GND), U1.D16 (GND), U1.D24 (GND), U1.D26 (GND), U1.D27 (GND), U1.D28 (GND), U1.D29 (GND), U1.E1 (GND), U1.E2 (GND), U1.E6 (GND), U1.E8 (GND), U1.E15 (GND), U1.F15 (GND), U1.F16 (GND), U1.F21 (GND), U1.F22 (GND), U1.G5 (GND), U1.G8 (GND), U1.G11 (GND), U1.G16 (GND), U1.G19 (GND), U1.G22 (GND), U1.G25 (GND), U1.G26 (GND), U1.G27 (GND), U1.G28 (GND), U1.H2 (GND), U1.H3 (GND), U1.H4 (GND), U1.H5 (GND), U1.H6 (GND), U1.H7 (GND), U1.H8 (GND), U1.H9 (GND), U1.H10 (GND), U1.H11 (GND), U1.H12 (GND), U1.H13 (GND), U1.H14 (GND), U1.H15 (GND), U1.H16 (GND), U1.H17 (GND), U1.H18 (GND), U1.H19 (GND), U1.H20 (GND), U1.H21 (GND), U1.H22 (GND), U1.H23 (GND), U1.H24 (GND), U1.H25 (GND), U1.H26 (GND), U1.H27 (GND), U1.H28 (GND), U1.H29 (GND), U1.M1 (GND), U1.T1 (GND), U1.Y29 (GND), U2.6 (ISNK_FINE), U2.19 (GND), U2.22 (GND), U2.25 (GND), U3.27 (GND), U4.1 (GND), U4.9 (GND), U5.12 (GND), U6.1 (GND), U6.5 (SDO), U6.7 (GND), U7.1 (GND), U7.2 (GND), U7.3 (GND), U7.4 (GND), U7.5 (GND), U7.6 (GND), U7.7 (GND), U7.8 (GND), U7.13 (GND), U7.14 (GND), U7.15 (GND), U7.19 (GND), U7.21 (GND), U7.22 (GND), U7.23 (GND), U7.26 (GND), U7.27 (GND), U7.28 (GND), U7.29 (GND), U7.30 (GND), U7.32 (ANT_CTRL), U7.33 (GND), U7.35 (GND), U7.37 (GND), U7.38 (GND), U7.40 (GND), U7.41 (GND), U7.42 (GND), U7.43 (GND), U7.44 (GND), U7.47 (GND), U7.48 (GND), U7.49 (GND), U7.50 (GND), U7.51 (GND), U7.54 (GND), U7.56 (GND), U9.9 (GND), U9.11 (GND), U10.3 (VSS), U10.8 (VSS), U10.9 (VSS)
/GNSS_PPS: U1.U29 (CAN1_RX), U7.20 (TIMEPULSE)
/GNSS_RXD: U1.AK24 (I2C3_SDA), U7.9 (RXD)
/GNSS_TXD: U1.AK25 (I2C3_SCL), U7.10 (TXD)
/I2C4_SCL: R26.2, U1.F28 (I2C4_SCL), U6.4 (SCK), U9.1 (SCL/SPI_SCK), U10.2 (SCK)
/I2C4_SDA: R25.2, U1.E29 (I2C4_SDA), U6.3 (SDI), U9.16 (SDA/SPI_SDI), U10.4 (SDI)
/ICM_CS: J1.7, U1.E19 (SPI8_CS0)
/ICM_INT1: J1.9, U1.E28 (GPIO2_IO22)
/ICM_INT2: J1.10, U1.E27 (GPIO2_IO23)
/ICM_MISO: J1.6, U1.E22 (SPI8_SIN)
/ICM_MOSI: J1.5, U1.E18 (SPI8_SOUT)
/ICM_SCLK: J1.3, U1.D17 (SPI8_SCK)
/ISNK_COARSE: R7.2, R8.1, U2.5 (ISNK_COARSE)
/LED_BLU_N: D4.1 (K), U1.R29 (CAN2_RX)
/LED_B_A: D4.2 (A), R30.2
/LED_GRN_N: D3.1 (K), U1.D18 (SPI1_SOUT)
/LED_G_A: D3.2 (A), R29.2
/LED_RED_N: D2.1 (K), U1.C18 (SPI1_SIN)
/LED_R_A: D2.2 (A), R28.2
/MAG_CAP: C18.1, U9.10 (CAP)
/NVCC_SD2: U1.F20 (MUX_3V3_1V8), U1.N1 (NVCC_SD2)
/ON_OFF_N: C17.1, R27.1, U1.AG18 (ON_OFF)
/ON_OFF_SW: R27.2, SW1.1
/OVP_FB: R20.2, R21.1, U5.16 (FB)
/OVP_FLT_N: U1.T29 (CAN1_TX), U5.13 (~FLT)
/OVP_HGATE: Q1.1 (G), U5.6 (HGATE)
/OVP_OV: R16.2, R17.1, U5.11 (OV)
/OVP_SENSE: Q1.2 (S), R22.1, U5.2 (SENSE), U5.5 (SOURCE)
/OVP_TMR: C5.1, U5.15 (TMR)
/OVP_UV: R18.2, R19.1, U5.10 (UV)
/PD_FAULT: U1.P29 (CAN2_TX), U2.9 (FAULT)
/PG_5V: R14.2, U4.4 (PG)
/REGN: C8.1, R1.1, R23.1, U3.5 (REGN)
/SD_VSELECT: U1.AH13 (SD_VSELECT), U1.AN5 (SD2_VSELECT)
/SW_5V: C3.2, L1.1, U4.8 (SW)
/VBAT: C11.1, J3.1, U3.22 (BAT), U3.23 (BAT)
/VBUS: C9.1, J2.A4 (VBUS), J2.A9 (VBUS), J2.B4 (VBUS), J2.B9 (VBUS), U2.18 (VBUS_IN), U3.2 (VBUS), U3.3 (VBUS), U3.9 (VAC1)
/VBUS_MAX: R5.2, R6.1, U2.2 (VBUS_MAX)
/VBUS_MIN: R3.2, R4.1, U2.1 (VBUS_MIN)
/VCC_BUCK: C4.1, U4.6 (VCC)
/VDDD: R3.1, R5.1, R7.1, U2.23 (VDDD)
/VSYS_CHG: C1.1, C12.1, U3.25 (SYS), U4.2 (VIN), U4.3 (EN)

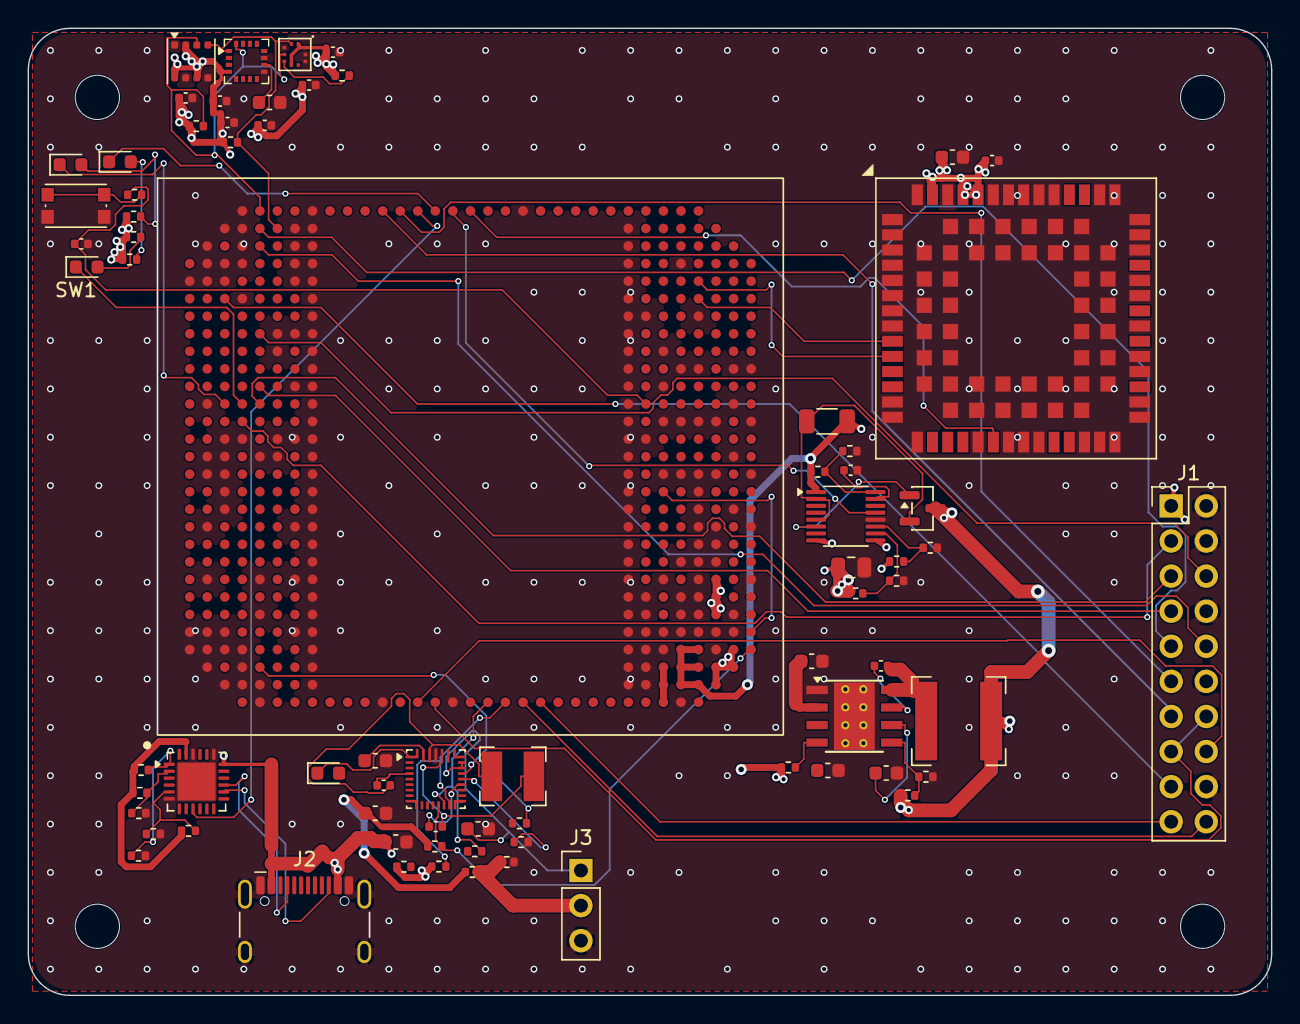
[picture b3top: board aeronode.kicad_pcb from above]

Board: 4 copper layers, 90.0 x 70.0 mm, 77 parts (0 on the bottom side), 71 nets.

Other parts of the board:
H1, H2, H3, H4: M3 NPTH; MountingHole_3.2mm_M3
